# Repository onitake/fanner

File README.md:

# fanner

Simple, microcontroller-based PWM fan controller.

Has customizable temperature and PWM ranges.

## Requirements

* make
* avr-libc
* avr-gcc
* KiCAD 4+

## Software

### Customize

Open fanner.c in a text editor and adapt the parameters near the top.

The predefined voltages are optimized for the MCP-7900 temperature sensor.

PWM output values depend on the FAN used and require some experimentation.

### Build

```bash
make
```

### Flash

```
make flash
```

### Code

The code heavily relies on compile-time optimiziation and precalculation
of the (linear) transfer function coefficients.

At runtime, only 16-bit multiplication and addition is used to transform
the the values sampled by the AD converter into PWM output values.

The transfer function is a very simple piecewise linear curve, represented
by the formula:

    Sd      := (Dhigh - Dlow) / (Thigh - Tlow)
    ADClow  := ADC(Tlow) = (Tlow * Ss + Vofs) / Vref * ADCmax
    ADChigh := ADC(Thigh) = (Thigh * Ss + Vofs) / Vref * ADCmax
    D(ADC)  := ADC <= ADClow          : Dlow
               ADC >= ADChigh         : Dhigh
               ADClow < ADC < ADChigh : [Vref / ADCmax / Ss * Sd] - [Vofs / Ss * Sd]

Where:

    D    : Output duty cycle (Dlow and Dhigh are the flat parts of the curve) [%]
    Vref : Sensor reference voltage (the voltage corresponding to ADCmax) [V]
    ADC  : Input value from AD converter (ADClow and ADChigh are the values at
           lowest and highest temperatures on the transfer curve, respectively;
           ADCmax is the value generated when reference voltage is measured) [1]
    T    : Sensor temperature (with Tlow and Thigh corresponding to the Dlow
           and Dhigh duty cycle values) [°C]
    Ss   : Sensor voltage slope [V/°C]
    Vofs : Sensor offset voltage (voltage at lowest temperature) [V]
    Sd   : Output slope [%/°C]

To reduce sudden jumps in fan speed, a ramping function is used. The RAMP_DELTA
and RAMP_DELAY parameters allow for tuning the ramping speed.

## Electronics

### Design

Use KiCAD version 4 or later.

The board layout is based on THT components for easier building. And because
I had the components lying around in my workshop.

If you want the board in SMD, you have to design it yourself.

### Circuit

The circuit is really simple and just consists of a small microcontroller
(the ATtiny13/A), a voltage regulator (fans usually run on 12V) and some
pin headers for connecting the sensor, power and the fan.

The button and the corresponding pull-up resistor as well as the debouncing
capacitor are optional and currently not used in the example code.

## Copyright

© 2018-2019 Gregor Riepl

PCB designs and schematics are licensed under the CERN Open Hardware License 1.2.
Program code and build scripts are licensed under the Simplified BSD License.

See the accompanying LICENSE-HARDWARE and LICENSE-SOFTWARE files for details.

All other rights are reserved.

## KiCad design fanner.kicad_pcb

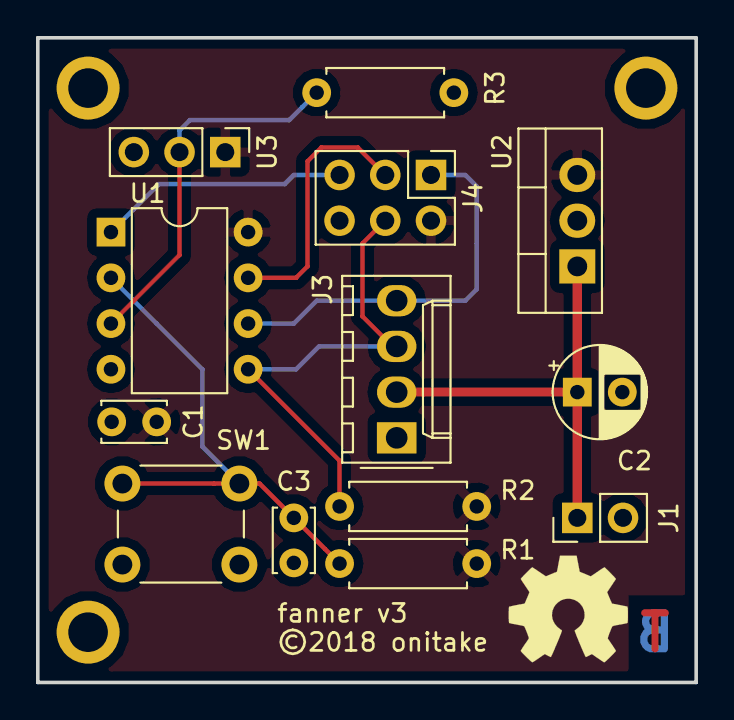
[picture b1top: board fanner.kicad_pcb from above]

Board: 2 copper layers, 36.6 x 35.8 mm, 16 parts (0 on the bottom side), 9 nets.

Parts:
C1: 100n; C_Disc_D3.4mm_W2.1mm_P2.50mm
C2: 10u; CP_Radial_D5.0mm_P2.50mm
C3: 10n; C_Disc_D3.4mm_W2.1mm_P2.50mm
J1: 12V PWR; PinHeader_1x02_P2.54mm_Vertical
J3: PWM OUT; Molex_KK-254_AE-6410-04A_1x04_P2.54mm_Vertical
J4: ISP; PinHeader_2x03_P2.54mm_Vertical
MH1, MH2, MH3: -; MountingHole_2.2mm_M2_ISO7380_Pad
R1, R2, R3: 10k; R_Axial_DIN0207_L6.3mm_D2.5mm_P7.62mm_Horizontal
SW1: MODE; SW_PUSH_6mm
U1: ATtiny13A-PU; DIP-8_W7.62mm
U2: LM2937IMP-5.0; TO-220-3_Vertical
U3: MCP9700-ETO; PinHeader_1x03_P2.54mm_Vertical

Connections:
+5V: C1.1, J4.2, R1.1, R2.1, U1.8, U2.3, U3.1
+12V: C2.1, J1.1, J3.2, U2.1
/MISO: J3.4, J4.1, U1.6
/MOSI: J3.3, J4.4, R2.2, U1.5
/SCK: J4.3, U1.7
/TEMP: R3.1, U1.3, U3.2
/~RESET: J4.5, U1.1
GND: C1.2, C2.2, C3.2, J1.2, J3.1, J4.6, R3.2, SW1.2, U1.4, U2.2, U3.3
unnamed: C3.1, R1.2, SW1.1, U1.2

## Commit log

2019-03-22 Initial version
2019-03-23 Improved documentation
2019-03-23 Further clarified values
2019-03-23 Corrected some typos and added missing formula

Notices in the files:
fanner.kicad_pcb:
© 2018 Gregor Riepl
©2018 onitake
